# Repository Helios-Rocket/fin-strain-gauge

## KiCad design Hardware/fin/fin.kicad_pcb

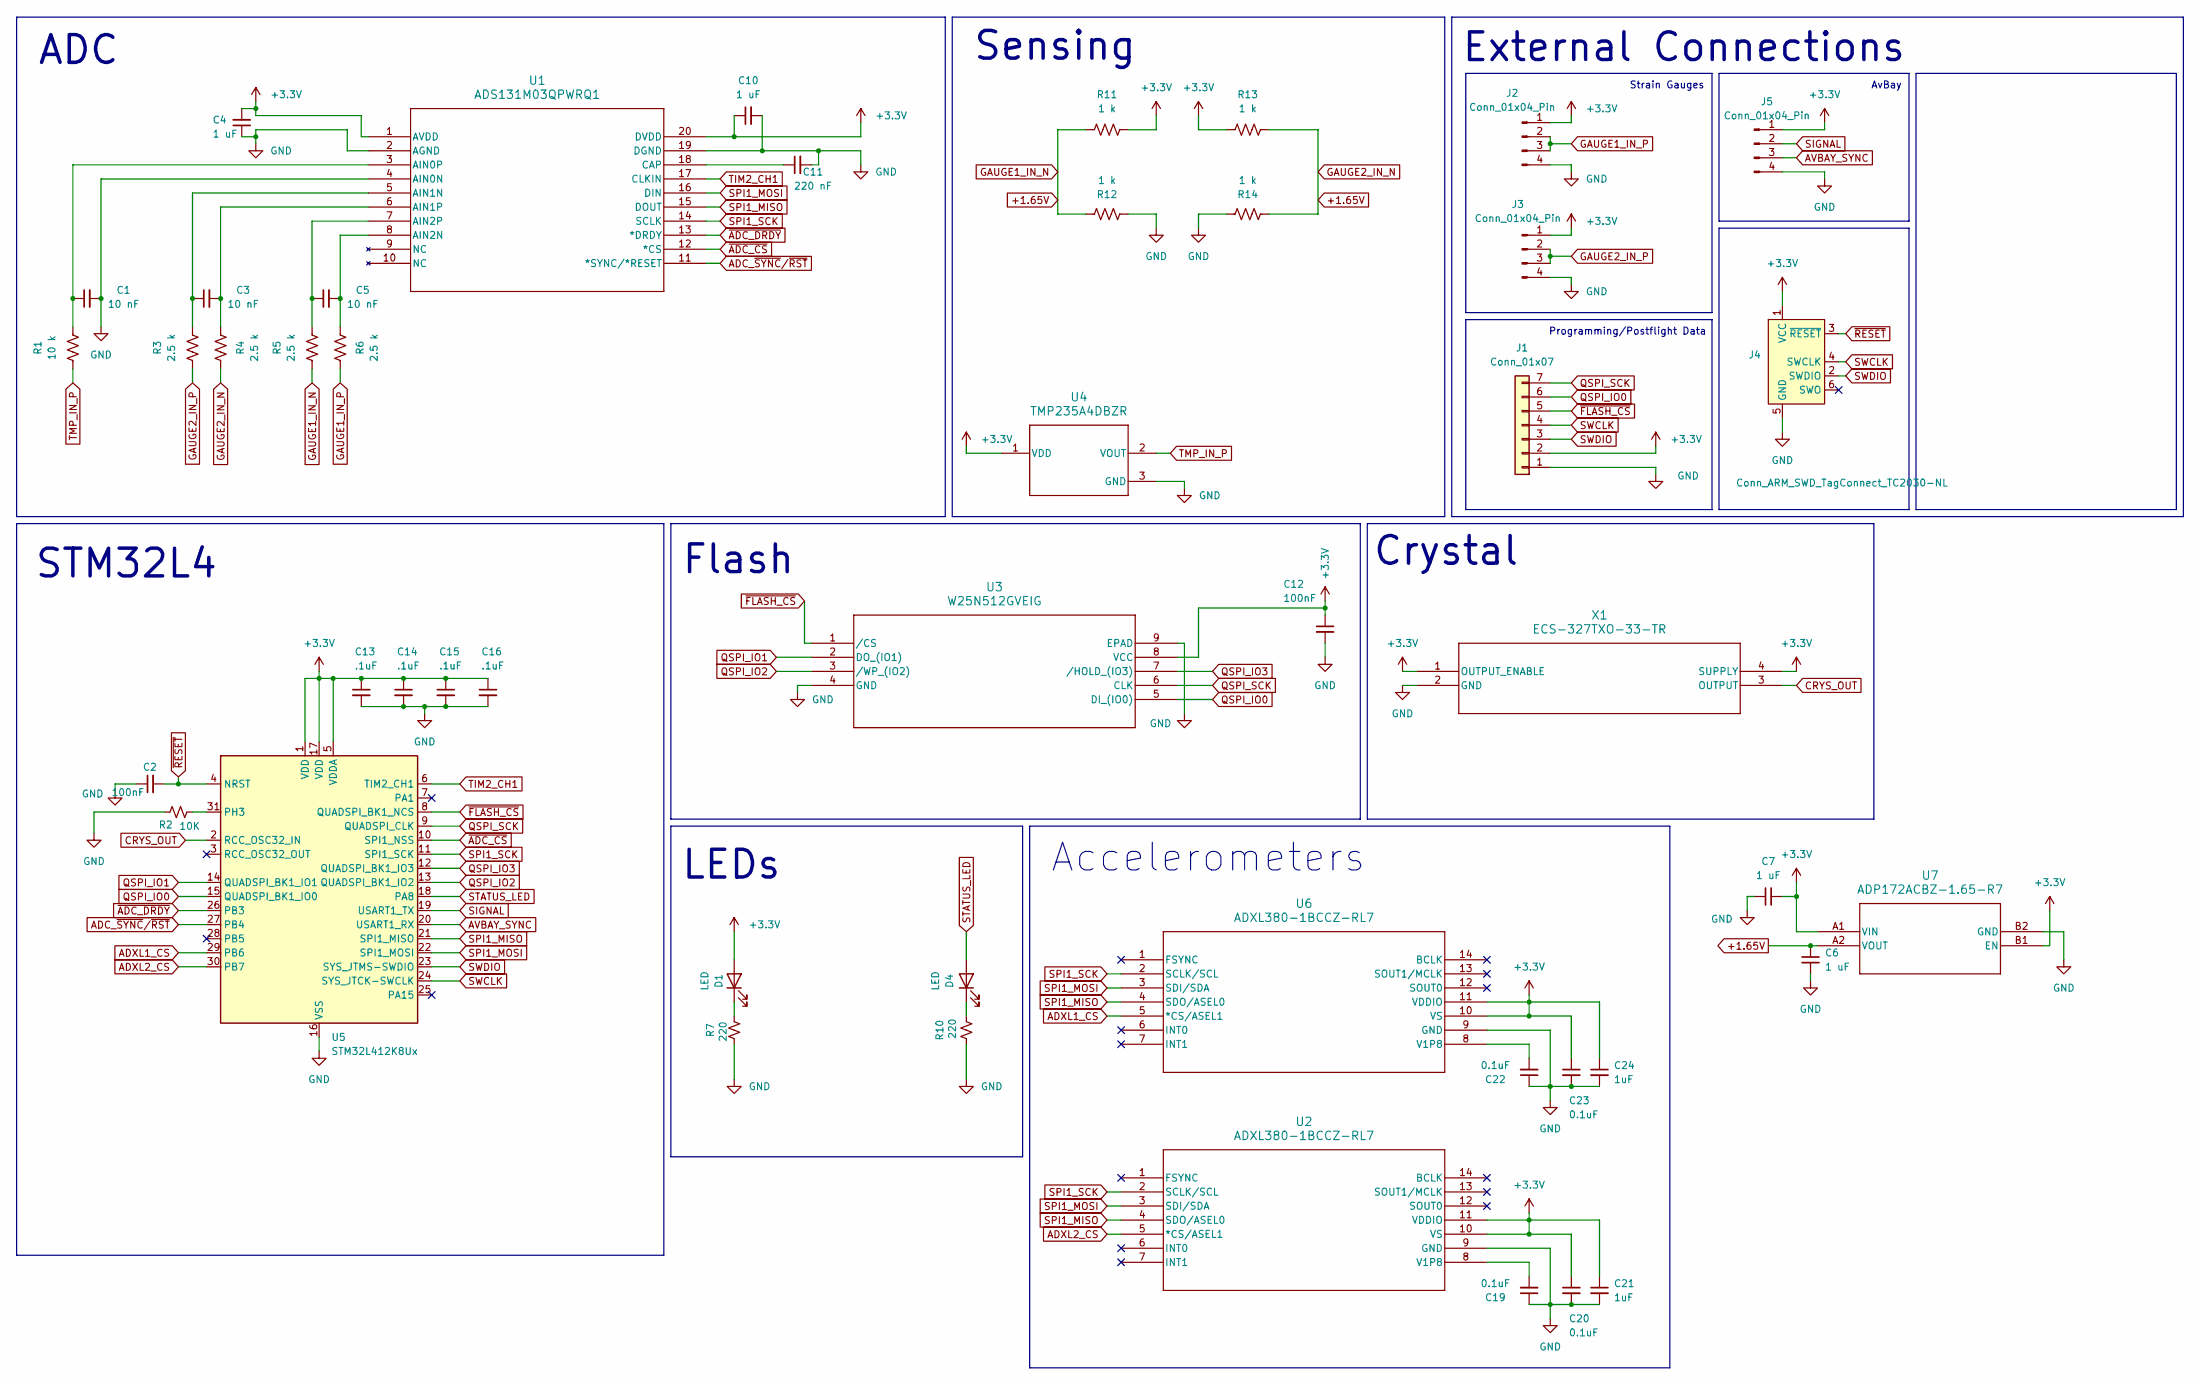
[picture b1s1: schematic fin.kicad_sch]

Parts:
C1, C3, C5: 10 nF; C_0402_1005Metric
C2, C12: 100nF; C_0402_1005Metric
C4, C6, C7, C10: 1 uF; C_0402_1005Metric
C11: 220 nF; C_0402_1005Metric
C13, C14, C15, C16: .1uF; C_0402_1005Metric
C19, C20, C22, C23: 0.1uF; C_0402_1005Metric
C21, C24: 1uF; C_0402_1005Metric
D1, D4: LED; LED_0402_1005Metric
J1: Conn_01x07; PinHeader_1x07_P2.54mm_Vertical
J2, J3: Conn_01x04_Pin; PinHeader_2x02_P2.54mm_Vertical
J4: Conn_ARM_SWD_TagConnect_TC2030-NL; Tag-Connect_TC2030-IDC-NL_2x03_P1.27mm_Vertical
J5: Conn_01x04_Pin; PinHeader_1x04_P2.54mm_Vertical
R1: 10 k; R_0402_1005Metric
R2: 10K; R_0402_1005Metric
R3, R4, R5, R6: 2.5 k; R_0402_1005Metric
R7, R10: 220; R_0402_1005Metric
R11, R12, R13, R14: 1 k; R_0402_1005Metric
U1: ADS131M03QPWRQ1; ADS131M03
U2, U6: ADXL380-1BCCZ-RL7; CC-14-3_ADI
U3: W25N512GVEIG; WSON8_8x6_E_WIN
U4: TMP235A4DBZR
U5: STM32L412K8Ux; QFN-32-1EP_5x5mm_P0.5mm_EP3.45x3.45mm
U7: ADP172ACBZ-1.65-R7; CB-4-4_ADI
X1: ECS-327TXO-33-TR; ECS-327_ECS

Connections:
+1.65V: C6.1, R4.2, R5.1, R11.1, R12.1, R13.2, R14.2, U7.A2 (VOUT)
+3.3V: C4.2, C7.2, C10.1, C12.1, C13.1, C14.1, C15.1, C16.1, C20.1, C21.1, C23.1, C24.1, D1.2 (A), J1.2, J2.1, J3.1, J4.1 (VCC), J5.1, R11.2, R13.1, U1.1 (AVDD), U1.20 (DVDD), U2.10 (VS), U2.11 (VDDIO), U3.8 (VCC), U4.1 (VDD), U5.1 (VDD), U5.5 (VDDA), U5.17 (VDD), U6.10 (VS), U6.11 (VDDIO), U7.A1 (VIN), U7.B1 (EN), X1.1 (OUTPUT_ENABLE), X1.4 (SUPPLY)
ADC_~SYNC/~RST: U1.11 (*SYNC/*RESET), U5.27 (PB4)
ADXL1_CS: U5.29 (PB6), U6.5 (*CS/ASEL1)
ADXL2_CS: U2.5 (*CS/ASEL1), U5.30 (PB7)
AVBAY_SYNC: J5.3, U5.20 (USART1_RX)
CRYS_OUT: U5.2 (RCC_OSC32_IN), X1.3 (OUTPUT)
GAUGE1_IN_P: J2.2, J2.3, R6.2
GAUGE2_IN_P: J3.2, J3.3, R3.1
GND: C1.2, C2.1, C4.1, C6.2, C7.1, C10.2, C11.2, C12.2, C13.2, C14.2, C15.2, C16.2, C19.1, C20.2, C21.2, C22.1, C23.2, C24.2, J1.1, J2.4, J3.4, J4.5 (GND), J5.4, R2.1, R7.2, R10.1, R12.2, R14.1, U1.2 (AGND), U1.4 (AIN0N), U1.19 (DGND), U2.9 (GND), U3.4 (GND), U3.9 (EPAD), U4.3 (GND), U5.16 (VSS), U5.32 (VSS), U5.33 (VSS), U6.9 (GND), U7.B2 (GND), X1.2 (GND)
unnamed: D1.1 (K), R7.1
unnamed: D4.1 (K), R10.2
unnamed: C1.1, R1.2, U1.3 (AIN0P)
unnamed: C3.1, R3.2, U1.5 (AIN1N)
unnamed: C3.2, R4.1, U1.6 (AIN1P)
unnamed: C5.2, R6.1, U1.8 (AIN2N)
unnamed: C5.1, R5.2, U1.7 (AIN2P)
unnamed: C11.1, U1.18 (CAP)
unnamed: C19.2, U2.8 (V1P8)
unnamed: R2.2, U5.31 (PH3)
unnamed: C22.2, U6.8 (V1P8)
QSPI_IO0: J1.6, U3.5 (DI_(IO0)), U5.15 (QUADSPI_BK1_IO0)
QSPI_IO1: U3.2 (DO_(IO1)), U5.14 (QUADSPI_BK1_IO1)
QSPI_IO2: U3.3 (/WP_(IO2)), U5.13 (QUADSPI_BK1_IO2)
QSPI_IO3: U3.7 (/HOLD_(IO3)), U5.12 (QUADSPI_BK1_IO3)
QSPI_SCK: J1.7, U3.6 (CLK), U5.9 (QUADSPI_CLK)
SIGNAL: J5.2, U5.19 (USART1_TX)
SPI1_MISO: U1.15 (DOUT), U2.4 (SDO/ASEL0), U5.21 (SPI1_MISO), U6.4 (SDO/ASEL0)
SPI1_MOSI: U1.16 (DIN), U2.3 (SDI/SDA), U5.22 (SPI1_MOSI), U6.3 (SDI/SDA)
SPI1_SCK: U1.14 (SCLK), U2.2 (SCLK/SCL), U5.11 (SPI1_SCK), U6.2 (SCLK/SCL)
STATUS_LED: D4.2 (A), U5.18 (PA8)
SWCLK: J1.4, J4.4 (SWCLK), U5.24 (SYS_JTCK-SWCLK)
SWDIO: J1.3, J4.2 (SWDIO), U5.23 (SYS_JTMS-SWDIO)
TIM2_CH1: U1.17 (CLKIN), U5.6 (TIM2_CH1)
TMP_IN_P: R1.1, U4.2 (VOUT)
~ADC_CS: U1.12 (*CS), U5.10 (SPI1_NSS)
~ADC_DRDY: U1.13 (*DRDY), U5.26 (PB3)
~FLASH_CS: J1.5, U3.1 (/CS), U5.8 (QUADSPI_BK1_NCS)
~RESET: C2.2, J4.3 (~RESET), U5.4 (NRST)

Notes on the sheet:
Strain Gauges
Flash
LEDs
Sensing
External Connections
ADC
STM32L4
Programming/Postflight Data
AvBay
Accelerometers
Crystal

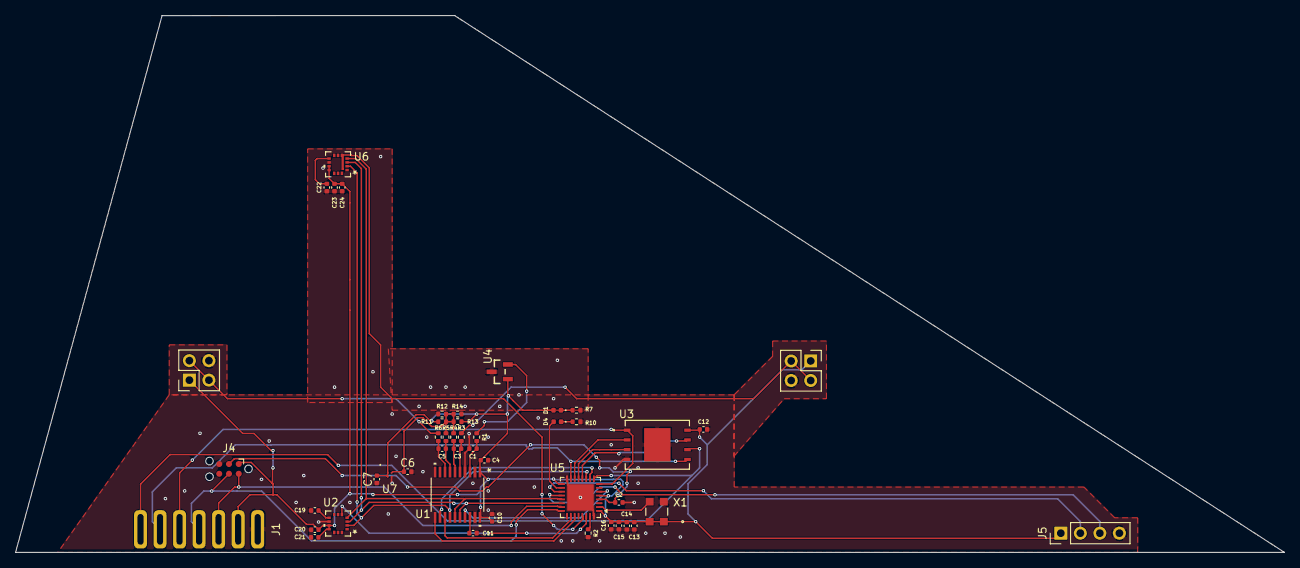
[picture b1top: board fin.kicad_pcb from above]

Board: 2 copper layers, 165.1 x 69.8 mm, 47 parts (0 on the bottom side), 39 nets.

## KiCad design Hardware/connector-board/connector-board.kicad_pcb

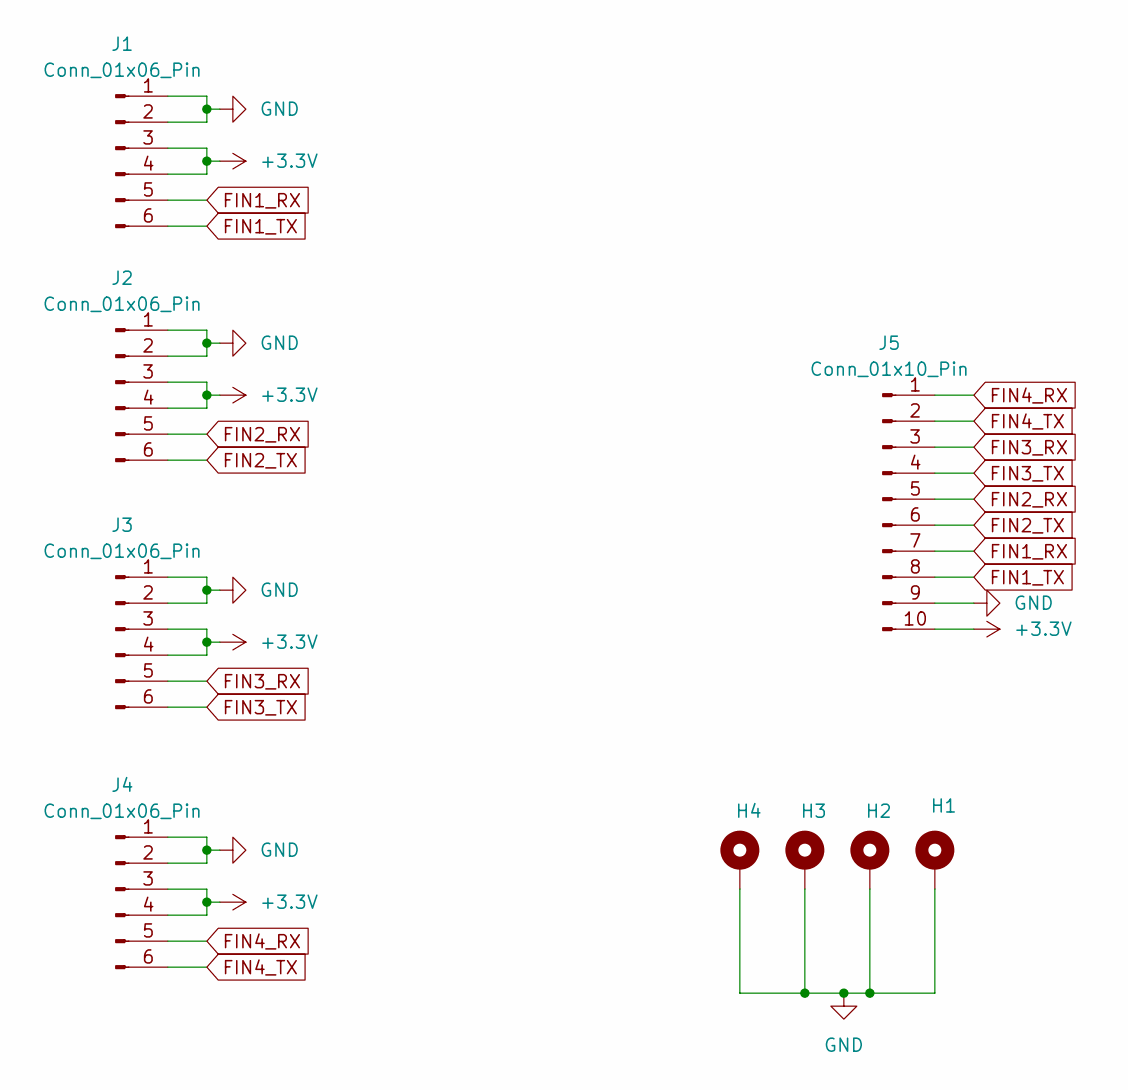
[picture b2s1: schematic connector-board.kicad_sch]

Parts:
H1, H2, H3, H4: MountingHole_Pad; MountingHole_2.2mm_M2_Pad
J1, J2, J3, J4: Conn_01x06_Pin; AMPHENOL_SFW6R-3STE1LF
J5: Conn_01x10_Pin; JST_ZE_BM10B-ZESS-TBT_1x10-1MP_P1.50mm_Vertical

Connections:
+3.3V: J1.3, J1.4, J2.3, J2.4, J3.3, J3.4, J4.3, J4.4, J5.10
FIN1_RX: J1.5, J5.7
FIN1_TX: J1.6, J5.8
FIN2_RX: J2.5, J5.5
FIN2_TX: J2.6, J5.6
FIN3_RX: J3.5, J5.3
FIN3_TX: J3.6, J5.4
FIN4_RX: J4.5, J5.1
FIN4_TX: J4.6, J5.2
GND: H1.1 (1_1), H2.1 (1_1), H3.1 (1_1), H4.1 (1_1), J1.1, J1.2, J2.1, J2.2, J3.1, J3.2, J4.1, J4.2, J5.9

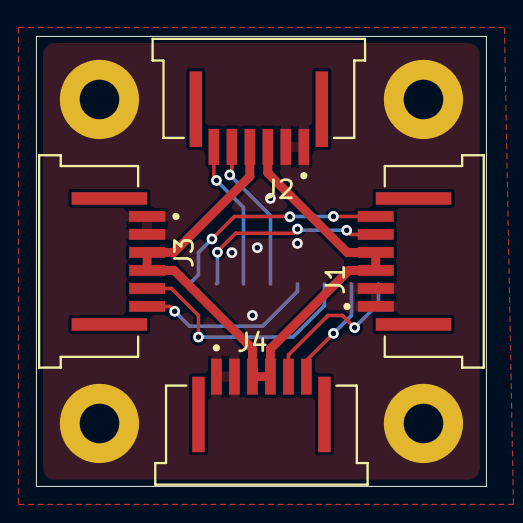
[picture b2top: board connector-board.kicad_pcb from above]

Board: 2 copper layers, 25.0 x 25.0 mm, 9 parts (1 on the bottom side), 10 nets.

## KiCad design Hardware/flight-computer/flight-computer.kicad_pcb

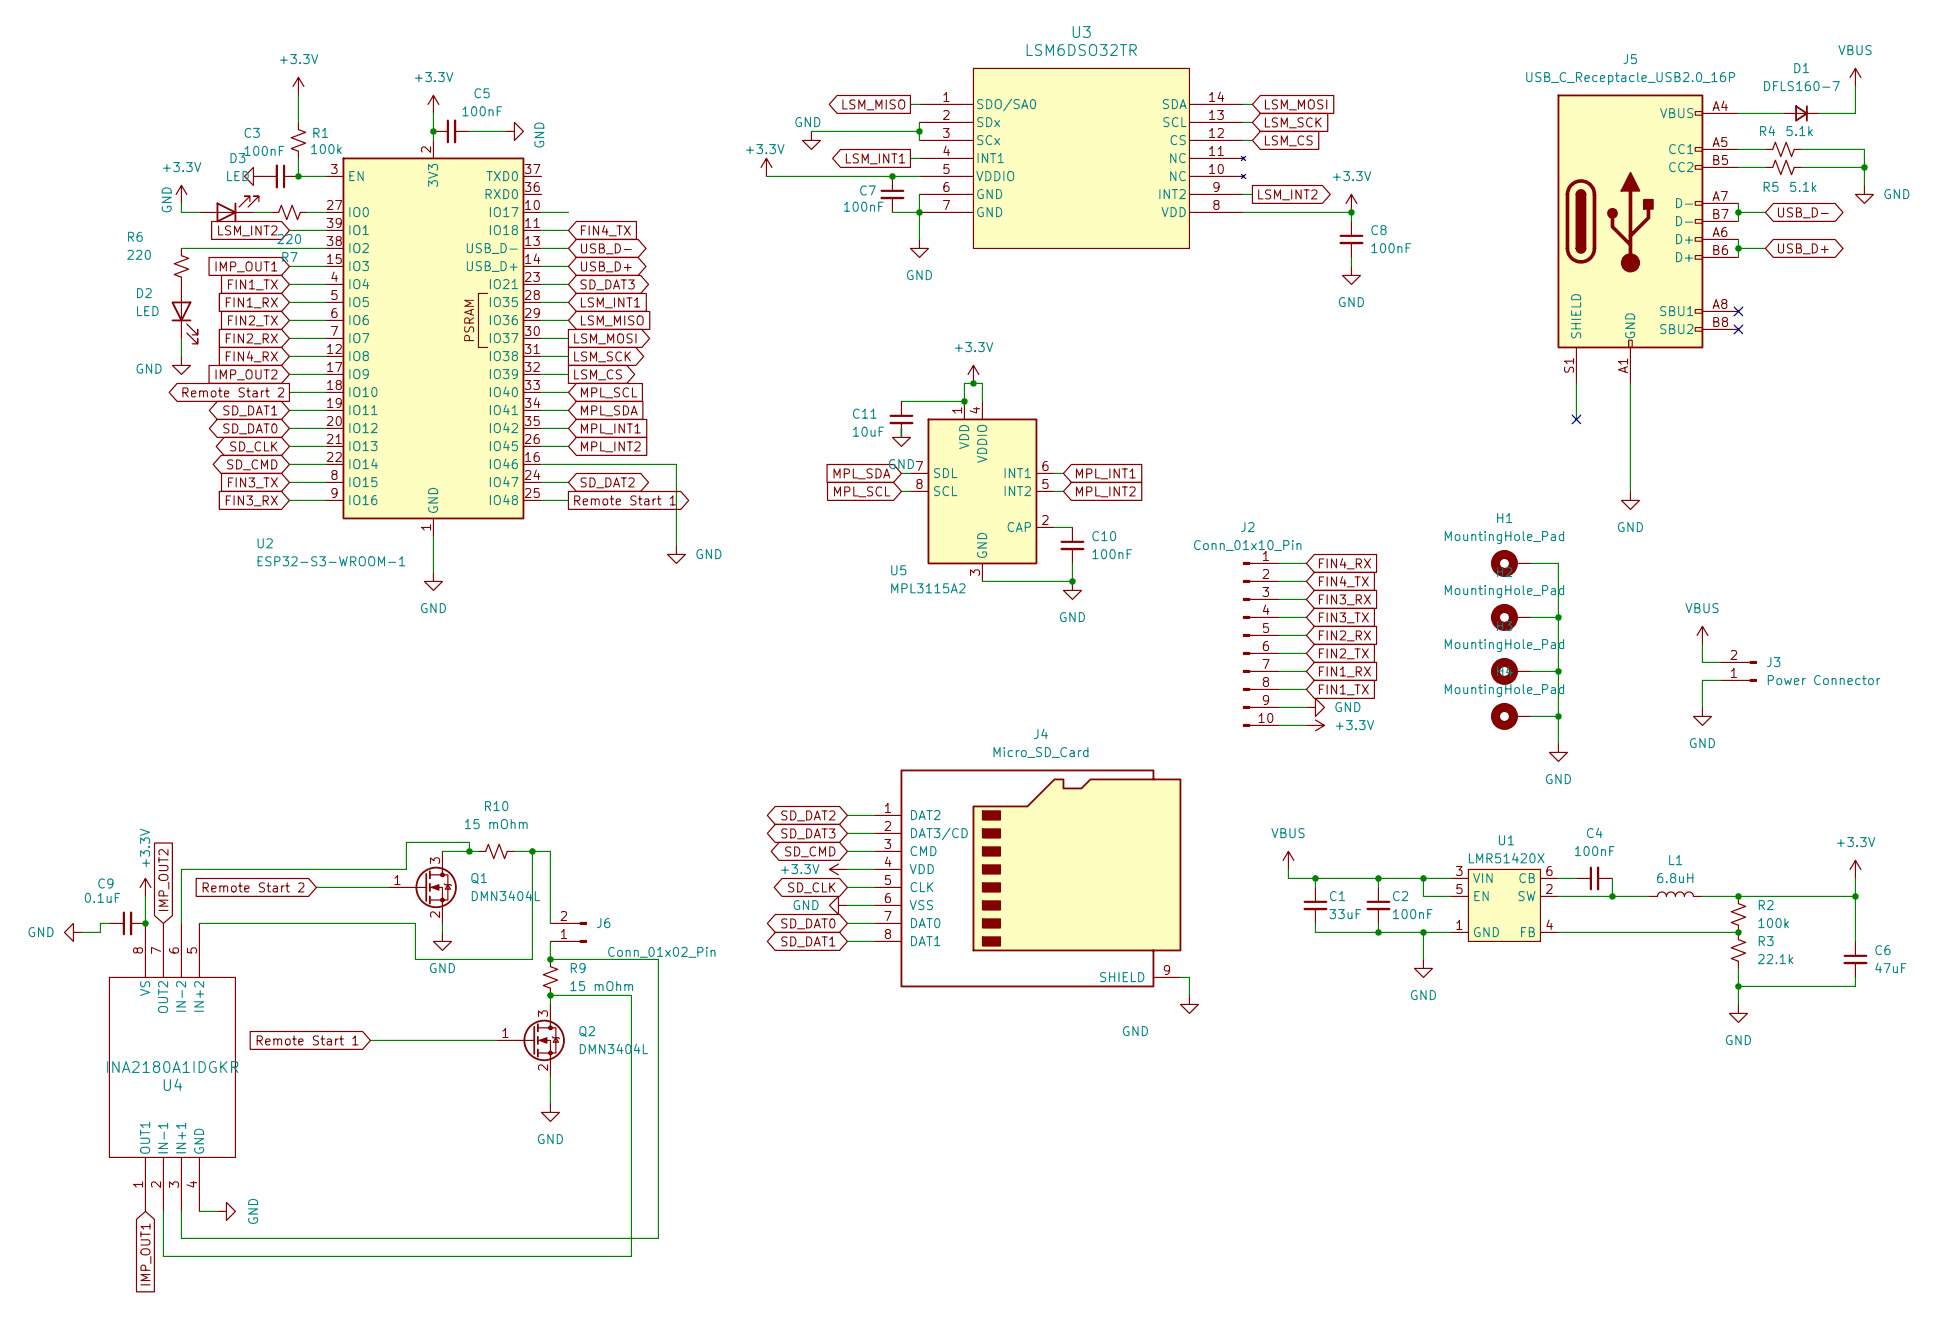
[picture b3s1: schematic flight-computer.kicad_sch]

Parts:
C1: 33uF; C_1206_3216Metric
C2, C3, C4, C5, C7, C8, C10: 100nF; C_0402_1005Metric
C6: 47uF; C_0402_1005Metric
C9: 0.1uF; C_0402_1005Metric
C11: 10uF; C_0402_1005Metric
D1: DFLS160-7; D_PowerDI-123
D2, D3: LED; LED_0603_1608Metric
H1, H2, H3, H4: MountingHole_Pad; MountingHole_2.2mm_M2_DIN965_Pad
J2: Conn_01x10_Pin; JST_ZE_SM10B-ZESS-TB_1x10-1MP_P1.50mm_Horizontal
J3: Power Connector; CONN2_282834-2_TEC
J4: Micro_SD_Card; CONN_MEM2067-02-180-00-A_GCT
J5: USB_C_Receptacle_USB2.0_16P; USB_C_Receptacle_GCT_USB4105-xx-A_16P_TopMnt_Horizontal
J6: Conn_01x02_Pin; CONN2_282834-2_TEC
L1: 6.8uH; IND_EXLA1V0505-220-R_EAT
Q1, Q2: DMN3404L; SOT-23
R1, R2: 100k; R_0402_1005Metric
R3: 22.1k; R_0402_1005Metric
R4, R5: 5.1k; R_0402_1005Metric
R6, R7: 220; R_0402_1005Metric
R9, R10: 15 mOhm; R_1206_3216Metric
U1: LMR51420X; SOT-23-6
U2: ESP32-S3-WROOM-1
U3: LSM6DSO32TR; LGA-14L_2P5X3X0P83_STM-M
U4: INA2180A1IDGKR; DGK8_TEX-M
U5: MPL3115A2; NXP_LGA-8_3x5mm_P1.25mm_H1.1mm

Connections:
+3.3V: C5.1, C6.1, C7.1, C8.1, C9.2, C11.1, D3.2 (A), J2.10, J4.4 (VDD), L1.2, R1.1, R2.1, U2.2 (3V3), U3.5 (VDDIO), U3.8 (VDD), U4.8 (VS), U5.1 (VDD), U5.4 (VDDIO)
FIN1_RX: J2.7, U2.5 (IO5)
FIN1_TX: J2.8, U2.4 (IO4)
FIN2_RX: J2.5, U2.7 (IO7)
FIN2_TX: J2.6, U2.6 (IO6)
FIN3_RX: J2.3, U2.9 (IO16)
FIN3_TX: J2.4, U2.8 (IO15)
FIN4_RX: J2.1, U2.12 (IO8)
FIN4_TX: J2.2, U2.11 (IO18)
GND: C1.2, C2.2, C3.2, C5.2, C6.2, C7.2, C8.2, C9.1, C10.2, C11.2, D2.1 (K), H1.1, H2.1, H3.1, H4.1, J2.9, J3.1, J4.6 (VSS), J4.9 (SHIELD), J5.A1 (GND), J5.A12 (GND), J5.B1 (GND), J5.B12 (GND), Q1.2 (S), Q2.2 (S), R3.2, R4.2, R5.2, U1.1 (GND), U2.1 (GND), U2.16 (IO46), U2.40 (GND), U2.41 (GND), U3.2 (SDx), U3.3 (SCx), U3.6 (GND), U3.7 (GND), U4.4 (GND), U5.3 (GND)
IMP_OUT1: U2.15 (IO3), U4.1 (OUT1)
IMP_OUT2: U2.17 (IO9), U4.7 (OUT2)
LSM_CS: U2.32 (IO39), U3.12 (CS)
LSM_INT1: U2.28 (IO35), U3.4 (INT1)
LSM_INT2: U2.39 (IO1), U3.9 (INT2)
LSM_MISO: U2.29 (IO36), U3.1 (SDO/SA0)
LSM_MOSI: U2.30 (IO37), U3.14 (SDA)
LSM_SCK: U2.31 (IO38), U3.13 (SCL)
MPL_INT1: U2.35 (IO42), U5.6 (INT1)
MPL_INT2: U2.26 (IO45), U5.5 (INT2)
MPL_SCL: U2.33 (IO40), U5.8 (SCL)
MPL_SDA: U2.34 (IO41), U5.7 (SDL)
unnamed: D1.2 (A), J5.A4 (VBUS), J5.A9 (VBUS), J5.B4 (VBUS), J5.B9 (VBUS)
unnamed: D2.2 (A), R6.2
unnamed: D3.1 (K), R7.2
unnamed: J5.A5 (CC1), R4.1
unnamed: J5.B5 (CC2), R5.1
unnamed: J6.1, R9.1, U4.3 (IN+1)
unnamed: J6.2, R10.2, U4.5 (IN+2)
unnamed: Q1.3 (D), R10.1, U4.6 (IN-2)
unnamed: Q2.3 (D), R9.2, U4.2 (IN-1)
unnamed: C4.1, U1.6 (CB)
unnamed: R2.2, R3.1, U1.4 (FB)
unnamed: C4.2, L1.1, U1.2 (SW)
unnamed: C3.1, R1.2, U2.3 (EN)
unnamed: R7.1, U2.27 (IO0)
unnamed: R6.1, U2.38 (IO2)
unnamed: C10.1, U5.2 (CAP)
Remote Start 1: Q2.1 (G), U2.25 (IO48)
Remote Start 2: Q1.1 (G), U2.18 (IO10)
SD_CLK: J4.5 (CLK), U2.21 (IO13)
SD_CMD: J4.3 (CMD), U2.22 (IO14)
SD_DAT0: J4.7 (DAT0), U2.20 (IO12)
SD_DAT1: J4.8 (DAT1), U2.19 (IO11)
SD_DAT2: J4.1 (DAT2), U2.24 (IO47)
SD_DAT3: J4.2 (DAT3/CD), U2.23 (IO21)
USB_D+: J5.A6 (D+), J5.B6 (D+), U2.14 (USB_D+)
USB_D-: J5.A7 (D-), J5.B7 (D-), U2.13 (USB_D-)
VBUS: C1.1, C2.1, D1.1 (K), J3.2, U1.3 (VIN), U1.5 (EN)

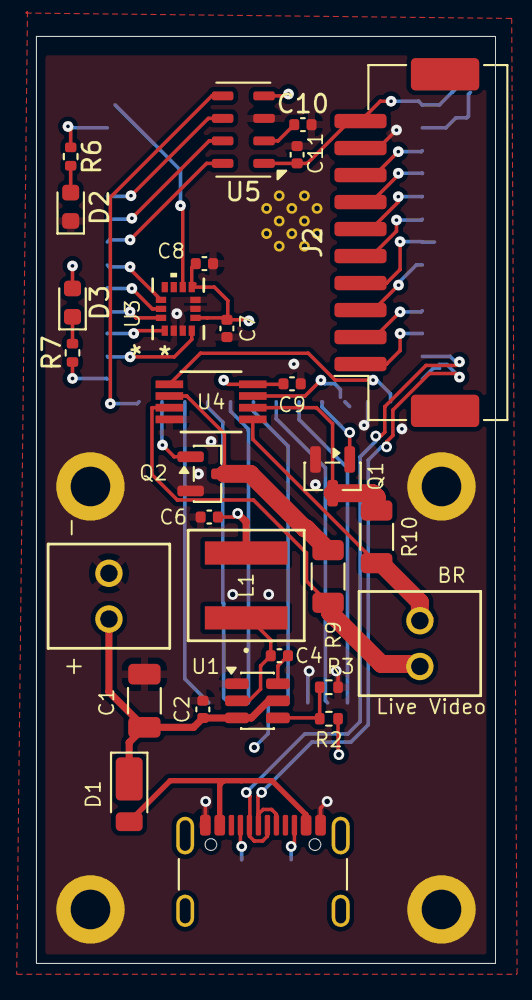
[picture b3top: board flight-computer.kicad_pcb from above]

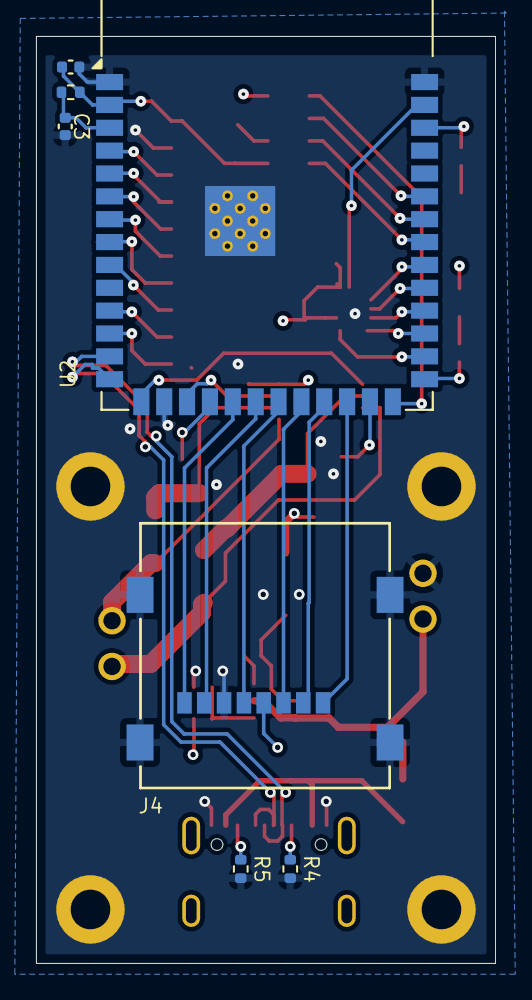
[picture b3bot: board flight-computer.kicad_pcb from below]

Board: 4 copper layers, 25.5 x 51.5 mm, 40 parts (7 on the bottom side), 49 nets.

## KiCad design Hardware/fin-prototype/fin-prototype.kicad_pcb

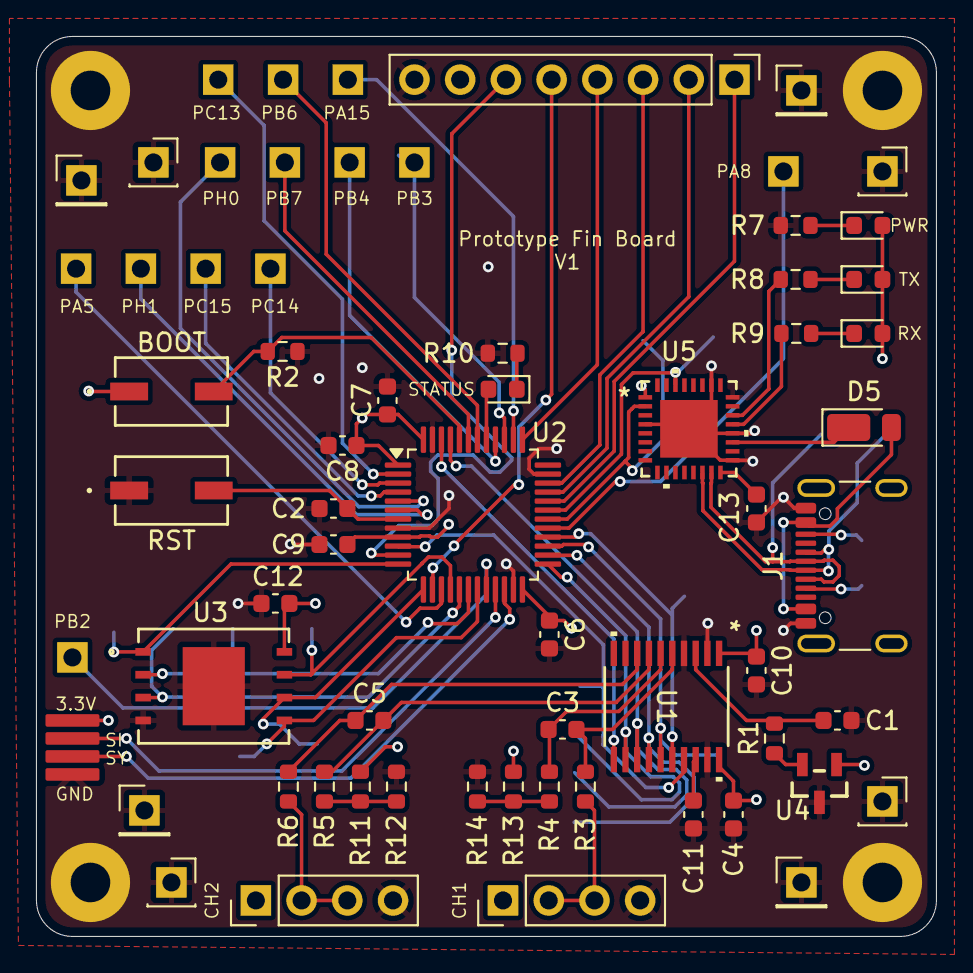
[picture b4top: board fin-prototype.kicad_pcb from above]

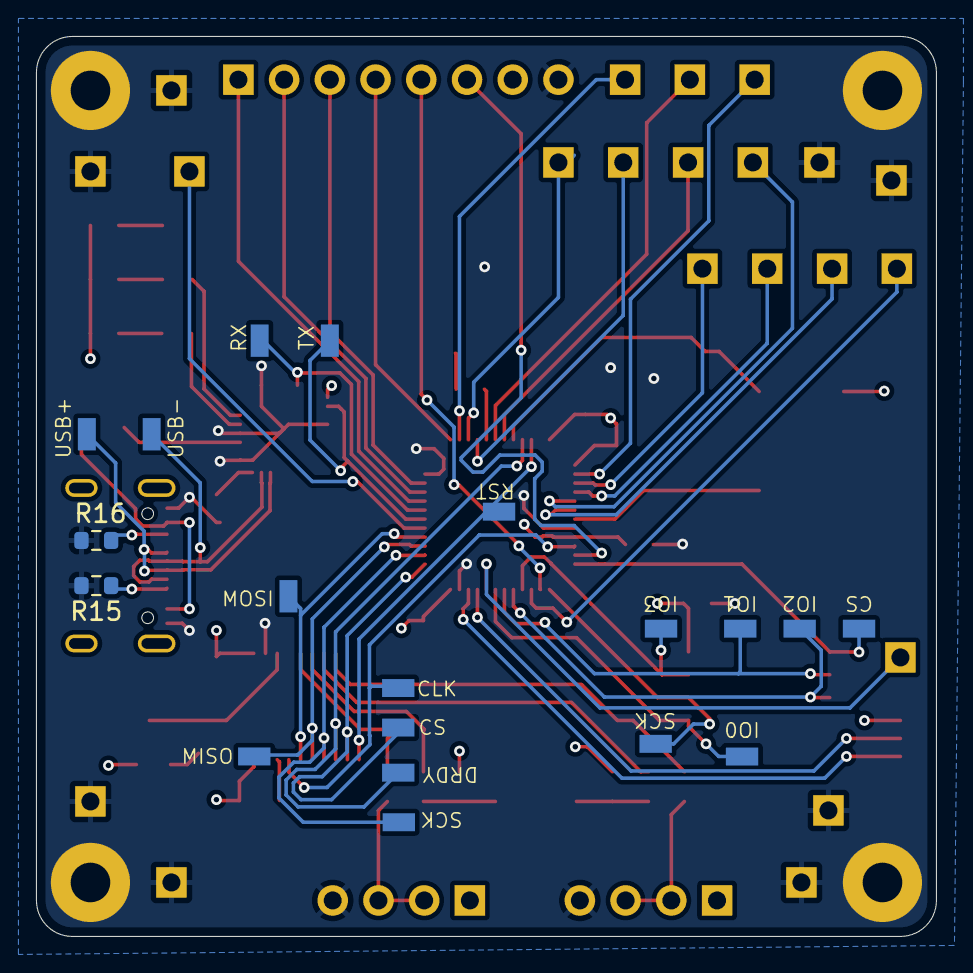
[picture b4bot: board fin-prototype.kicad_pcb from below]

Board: 4 copper layers, 50.0 x 50.0 mm, 88 parts (19 on the bottom side), 65 nets.

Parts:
C1, C3, C5: 10 nF; C_0603_1608Metric
C2, C6, C7, C8, C9, C12, C13: 100nF; C_0603_1608Metric
C4, C10: 1 uF; C_0603_1608Metric
C11: 220 nF; C_0603_1608Metric
D1, D2, D3, D4: LED; LED_0603_1608Metric
D5: DFLS160-7; D_PowerDI-123
H1, H2, H3, H4: MountingHole_Pad; MountingHole_2.2mm_M2_Pad
J1: USB_C_Receptacle_USB2.0_16P; USB_C_Receptacle_GCT_USB4105-xx-A_16P_TopMnt_Horizontal
J2, J3: Conn_01x04_Pin; PinHeader_1x04_P2.54mm_Vertical
J4: Conn_01x08_Pin; PinHeader_1x08_P2.54mm_Vertical
J5: Conn_01x04_Pin; FlexCable
J6, J7, J8, J9, J10, J11, J12, J13, J14, J15, J16, J17, J18: Conn_01x01_Pin; SimpleThroughHole
R1: 10 k; R_0603_1608Metric
R2: 5K; R_0603_1608Metric
R3, R4, R5, R6: 2.5 k; R_0603_1608Metric
R7, R8, R9, R10: 220; R_0603_1608Metric
R11, R12, R13, R14: 1 k; R_0603_1608Metric
R15, R16: 5.1k; R_0603_1608Metric
SW1, SW2: SW_Push; SW_FSM2JMTR_TEC
TP1, TP2, TP3, TP4: TestPoint; PinHeader_1x01_P2.54mm_Vertical
TP5, TP6, TP7, TP8: TestPoint; PinSocket_1x01_P2.54mm_Vertical
TP9, TP10, TP11, TP12, TP13, TP14, TP15, TP16, TP17, TP18, TP19, TP20, TP21, TP22, TP23, TP24, TP25: TestPoint
U1: ADS131M03QPWRQ1; ADS131M03
U2: STM32L412C8Tx; LQFP-48_7x7mm_P0.5mm
U3: W25N512GVEIG; WSON8_8x6_E_WIN
U4: TMP235A4DBZR
U5: FT232RNQ-REEL; QFN32_FT232_FTD

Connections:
+3.3V: C4.2, C6.1, C7.1, C8.1, C9.1, C10.1, C12.1, D1.2 (A), D2.2 (A), D3.2 (A), J2.1, J3.1, J4.7, J5.1, R11.2, R13.1, SW2.1, U1.1 (AVDD), U1.20 (DVDD), U2.1 (VBAT), U2.9 (VDDA), U2.24 (VDD), U2.48 (VDD), U3.8 (VCC), U4.1 (VDD), U5.1 (VCCIO)
+5V: D5.1 (K), U5.19 (VCC)
ADC_~SYNC/~RST: TP14.1, U1.11 (*SYNC/*RESET), U2.46 (PB9)
AVBAY_SYNC: J5.3, U2.22 (PB11)
GAUGE1_IN_N: R5.1, R11.1, R12.1
GAUGE1_IN_P: J2.2, J2.3, R6.2
GAUGE2_IN_N: R4.2, R13.2, R14.2
GAUGE2_IN_P: J3.2, J3.3, R3.1
GND: C1.2, C2.1, C4.1, C6.2, C7.2, C8.2, C9.2, C10.2, C11.2, C12.2, C13.2, H1.1, H2.1, H3.1, H4.1, J1.A1 (GND), J1.A12 (GND), J1.B1 (GND), J1.B12 (GND), J2.4, J3.4, J4.8, J5.4, R2.1, R7.2, R10.1, R12.2, R14.1, R15.2, R16.2, SW1.1, TP1.1, TP2.1, TP3.1, TP4.1, TP5.1, TP6.1, TP7.1, TP8.1, U1.2 (AGND), U1.4 (AIN0N), U1.19 (DGND), U2.8 (VSSA), U2.23 (VSS), U2.35 (VSS), U2.47 (VSS), U3.4 (GND), U3.9 (EPAD), U4.3 (GND), U5.4 (GND), U5.17 (GND), U5.20 (GND), U5.24 (AGND), U5.26 (TEST), U5.33 (EPAD)
unnamed: D1.1 (K), R7.1
unnamed: D2.1 (K), R8.2
unnamed: D3.1 (K), R9.2
unnamed: D4.1 (K), R10.2
unnamed: D5.2 (A), J1.A4 (VBUS), J1.A9 (VBUS), J1.B4 (VBUS), J1.B9 (VBUS)
unnamed: J1.A5 (CC1), R15.1
unnamed: J1.B5 (CC2), R16.1
unnamed: C1.1, R1.2, U1.3 (AIN0P)
unnamed: C3.1, R3.2, U1.5 (AIN1N)
unnamed: C3.2, R4.1, U1.6 (AIN1P)
unnamed: C5.2, R6.1, U1.8 (AIN2N)
unnamed: C5.1, R5.2, U1.7 (AIN2P)
unnamed: C11.1, U1.18 (CAP)
unnamed: C2.2, SW1.2, U2.7 (NRST)
unnamed: R2.2, SW2.2, U2.44 (PH3)
unnamed: C13.1, U5.16 (3V3OUT)
PA5: J6.1, U2.15 (PA5)
PA8: J7.1, U2.29 (PA8)
PA15: J8.1, U2.38 (PA15)
PB2: J9.1, U2.20 (PB2)
PB3: J10.1, U2.39 (PB3)
PB4: J11.1, U2.40 (PB4)
PB6: J12.1, U2.42 (PB6)
PB7: J13.1, U2.43 (PB7)
PC13: J14.1, U2.2 (PC13)
PC14: J15.1, U2.3 (PC14)
PC15: J16.1, U2.4 (PC15)
PH0: J17.1, U2.5 (PH0)
PH1: J18.1, U2.6 (PH1)
QSPI_IO0: TP17.1, U2.19 (PB1), U3.5 (DI_(IO0))
QSPI_IO1: TP18.1, U2.18 (PB0), U3.2 (DO_(IO1))
QSPI_IO2: TP19.1, U2.17 (PA7), U3.3 (/WP_(IO2))
QSPI_IO3: TP20.1, U2.16 (PA6), U3.7 (/HOLD_(IO3))
QSPI_SCK: TP16.1, U2.13 (PA3), U3.6 (CLK)
SIGNAL: J5.2, U2.21 (PB10)
SPI1_MISO: J4.1, U2.32 (PA11)
SPI1_MOSI: J4.2, U2.33 (PA12)
SPI1_SCK: J4.6, U2.11 (PA1)
SPI2_MISO: TP10.1, U1.15 (DOUT), U2.27 (PB14)
SPI2_MOSI: TP11.1, U1.16 (DIN), U2.28 (PB15)
SPI2_SCK: TP9.1, U1.14 (SCLK), U2.26 (PB13)
STATUS_LED: D4.2 (A), U2.41 (PB5)
SWCLK: J4.4, U2.37 (PA14)
SWDIO: J4.3, U2.34 (PA13)
TIM2_CH1: TP13.1, U1.17 (CLKIN), U2.10 (PA0)
TMP_IN_P: R1.1, U4.2 (VOUT)
USART1_RX: TP22.1, U2.31 (PA10), U5.30 (TXD)
USART1_TX: TP23.1, U2.30 (PA9), U5.2 (RXD)
USB_D+: J1.A6 (D+), J1.B6 (D+), TP24.1, U5.14 (USBDP)
USB_D-: J1.A7 (D-), J1.B7 (D-), TP25.1, U5.15 (USBDM)
~ADC_CS: TP12.1, U1.12 (*CS), U2.25 (PB12)
~ADC_DRDY: TP15.1, U1.13 (*DRDY), U2.45 (PB8)
~FLASH_CS: TP21.1, U2.12 (PA2), U3.1 (/CS)
~RX_LED: R9.1, U5.21 (CBUS1)
~SPI1_CS: J4.5, U2.14 (PA4)
~TX_LED: R8.1, U5.22 (CBUS0)

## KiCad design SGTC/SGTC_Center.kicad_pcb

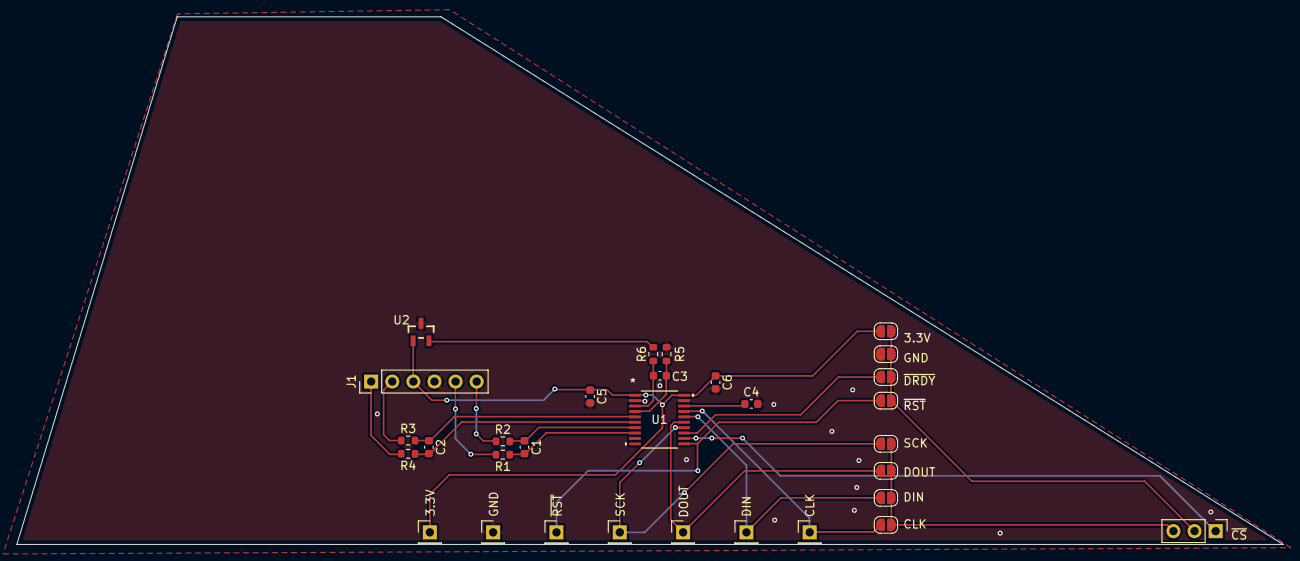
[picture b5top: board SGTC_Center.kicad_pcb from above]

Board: 2 copper layers, 152.4 x 63.5 mm, 31 parts (0 on the bottom side), 23 nets.

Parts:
C1, C2, C3: 10 nF; C_0603_1608Metric
C4: 220 nF; C_0603_1608Metric
C5, C6: 1 uF; C_0603_1608Metric
J1: Conn_01x06_Pin; PinHeader_1x06_P2.54mm_Vertical
J2, J4, J5, J6, J7, J8, J9: Conn_01x01_Pin; PinHeader_1x01_P2.54mm_Vertical
J3: Conn_01x03_Pin; PinHeader_1x03_P2.54mm_Vertical
JP1, JP2, JP3, JP4, JP5, JP6, JP7, JP8: SolderJumper_2_Open; SolderJumper-2_P1.3mm_Open_RoundedPad1.0x1.5mm
R1, R2, R3, R4, R5, R6: 10 k; R_0603_1608Metric
U1: ADS131M03QPWRQ1; ADS131M03
U2: TMP235A4DBZR

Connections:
+3.3V: C5.1, C6.1, J1.3, J9.1, JP7.2 (B), U1.1 (AVDD), U1.20 (DVDD), U2.1 (VDD)
ADCCLK: J2.1, JP1.2 (B), U1.17 (CLKIN)
DIN: J4.1, JP2.2 (B), U1.16 (DIN)
DOUT: J5.1, JP3.2 (B), U1.15 (DOUT)
GAUGE1_IN_N: J1.1, R4.2
GAUGE1_IN_P: J1.2, R3.1
GAUGE2_IN_N: J1.5, R1.2
GAUGE2_IN_P: J1.6, R2.1
GND: C4.2, C5.2, C6.2, J1.4, J8.1, JP6.2 (B), R6.2, U1.2 (AGND), U1.19 (DGND), U2.3 (GND)
unnamed: J3.2, JP5.1 (A), JP6.1 (A), JP7.1 (A), JP8.1 (A)
unnamed: J3.3, JP1.1 (A), JP2.1 (A), JP3.1 (A), JP4.1 (A)
unnamed: C3.2, R6.1, U1.4 (AIN0N)
unnamed: C3.1, R5.2, U1.3 (AIN0P)
unnamed: C2.1, R3.2, U1.5 (AIN1N)
unnamed: C2.2, R4.1, U1.6 (AIN1P)
unnamed: C1.2, R1.1, U1.8 (AIN2N)
unnamed: C1.1, R2.2, U1.7 (AIN2P)
unnamed: C4.1, U1.18 (CAP)
SPICLK: J6.1, JP4.2 (B), U1.14 (SCLK)
TMP_IN_P: R5.1, U2.2 (VOUT)
~CS: J3.1, U1.12 (*CS)
~DRDY: JP8.2 (B), U1.13 (*DRDY)
~SYNC/~RST: J7.1, JP5.2 (B), U1.11 (*SYNC/*RESET)

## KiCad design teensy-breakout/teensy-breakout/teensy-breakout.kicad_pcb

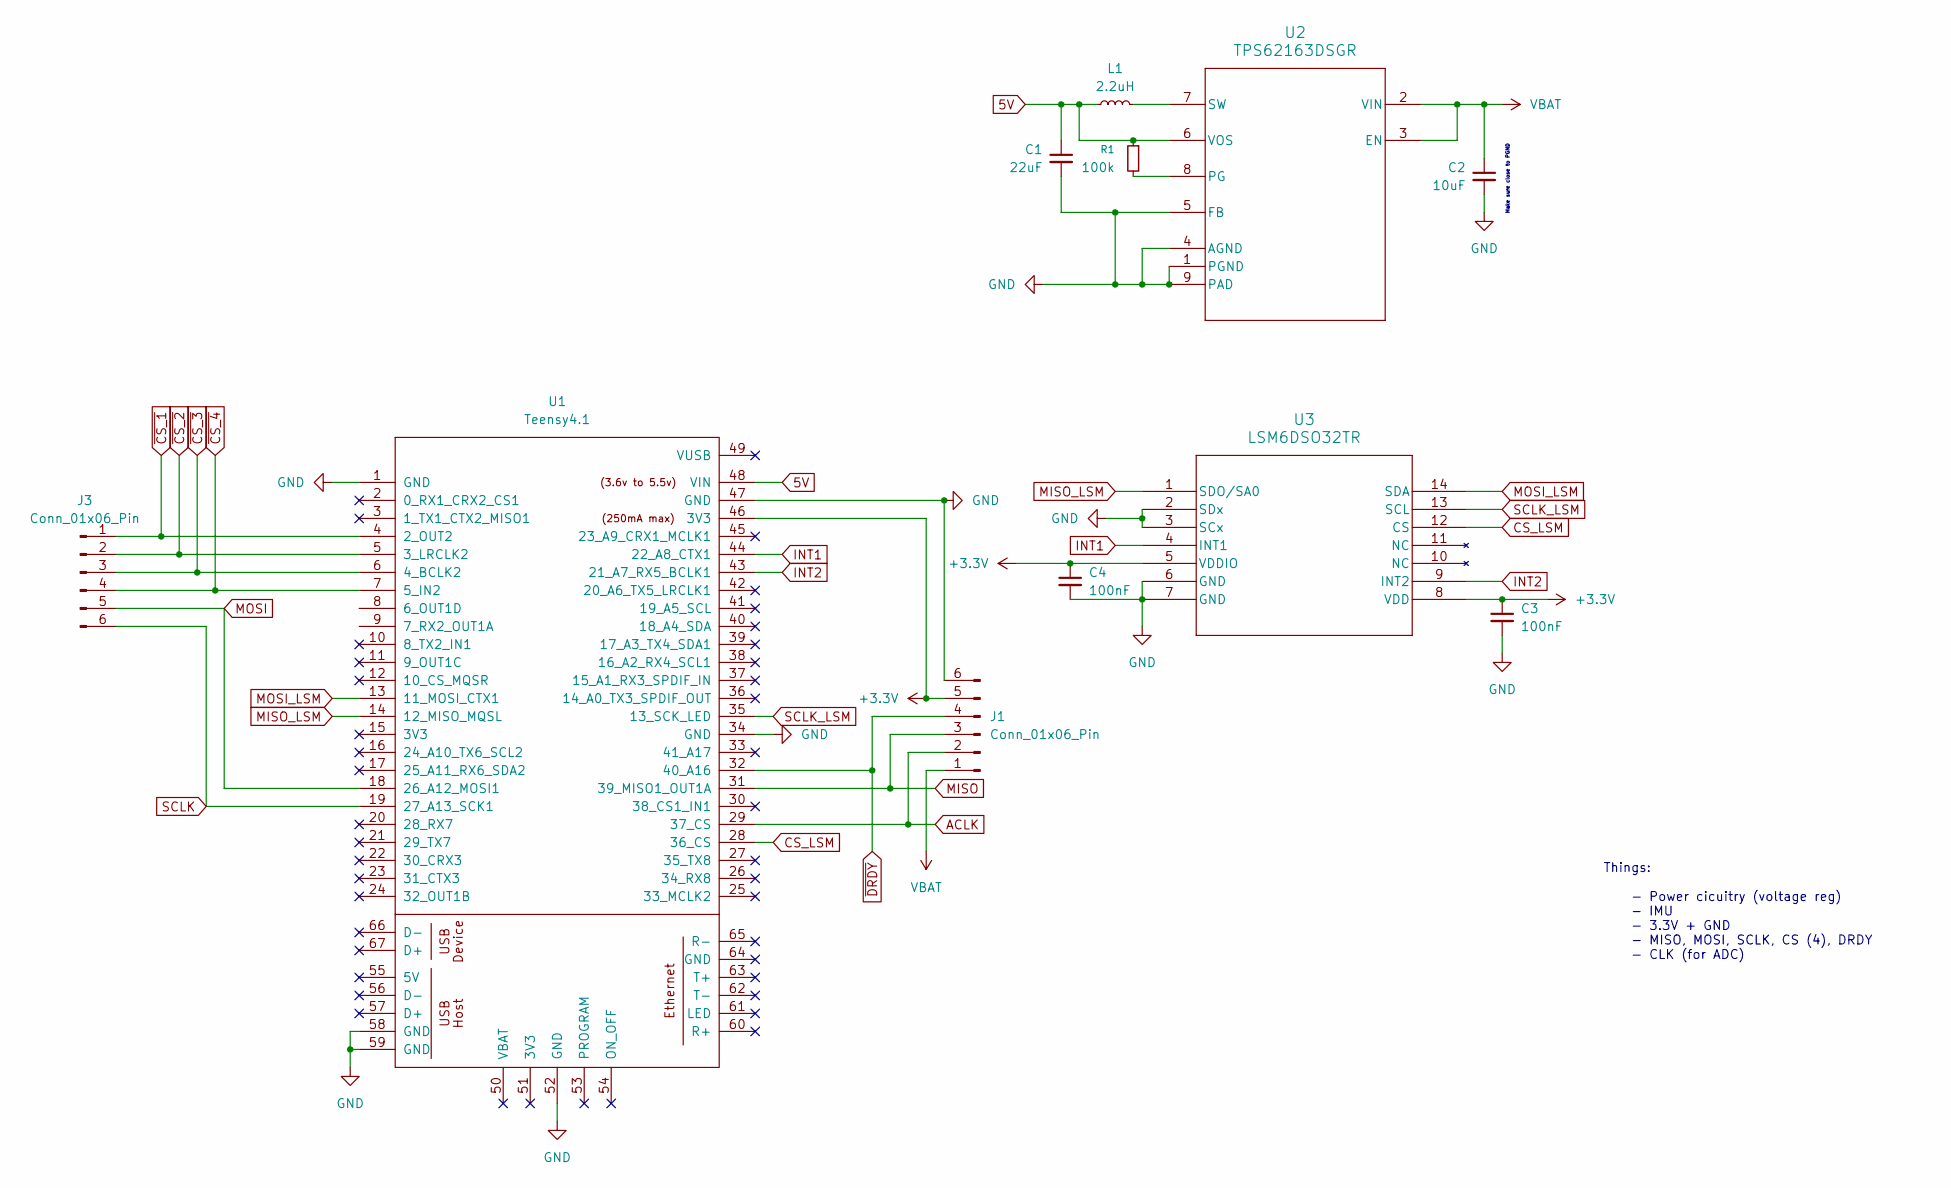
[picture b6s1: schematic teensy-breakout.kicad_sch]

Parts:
C1: 22uF; C_0805_2012Metric
C2: 10uF; C_0805_2012Metric
C3, C4: 100nF; C_0603_1608Metric
J1, J3: Conn_01x06_Pin; PinHeader_1x06_P2.54mm_Vertical
L1: 2.2uH; LCXHF3030QKT2R2MNR
R1: 100k; R_0603_1608Metric
U1: Teensy4.1; Teensy41
U2: TPS62163DSGR; TPS62163
U3: LSM6DSO32TR; LSM6DSO32

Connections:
5V: C1.1, L1.2, R1.1, U1.48 (VIN), U2.6 (VOS)
+3.3V: C3.1, C4.1, J1.5, U1.46 (3V3), U3.5 (VDDIO), U3.8 (VDD)
ACLK: J1.2, U1.29 (37_CS)
CS_LSM: U1.28 (36_CS), U3.12 (CS)
GND: C1.2, C2.2, C3.2, C4.2, J1.6, U1.1 (GND), U1.34 (GND), U1.47 (GND), U1.52 (GND), U1.58 (GND), U1.59 (GND), U2.1 (PGND), U2.4 (AGND), U2.5 (FB), U2.9 (PAD), U3.2 (SDx), U3.3 (SCx), U3.6 (GND), U3.7 (GND)
INT1: U1.44 (22_A8_CTX1), U3.4 (INT1)
INT2: U1.43 (21_A7_RX5_BCLK1), U3.9 (INT2)
MISO: J1.3, U1.31 (39_MISO1_OUT1A)
MISO_LSM: U1.14 (12_MISO_MQSL), U3.1 (SDO/SA0)
MOSI: J3.5, U1.18 (26_A12_MOSI1)
MOSI_LSM: U1.13 (11_MOSI_CTX1), U3.14 (SDA)
unnamed: R1.2, U2.8 (PG)
unnamed: L1.1, U2.7 (SW)
SCLK: J3.6, U1.19 (27_A13_SCK1)
SCLK_LSM: U1.35 (13_SCK_LED), U3.13 (SCL)
VBAT: C2.1, J1.1, U2.2 (VIN), U2.3 (EN)
~CS_1: J3.1, U1.4 (2_OUT2)
~CS_2: J3.2, U1.5 (3_LRCLK2)
~CS_3: J3.3, U1.6 (4_BCLK2)
~CS_4: J3.4, U1.7 (5_IN2)
~DRDY: J1.4, U1.32 (40_A16)

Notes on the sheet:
Things: - Power cicuitry (voltage reg) - IMU - 3.3V + GND - MISO, MOSI, SCLK, CS (4), DRDY - CLK (for ADC)
Make sure close to PGND
